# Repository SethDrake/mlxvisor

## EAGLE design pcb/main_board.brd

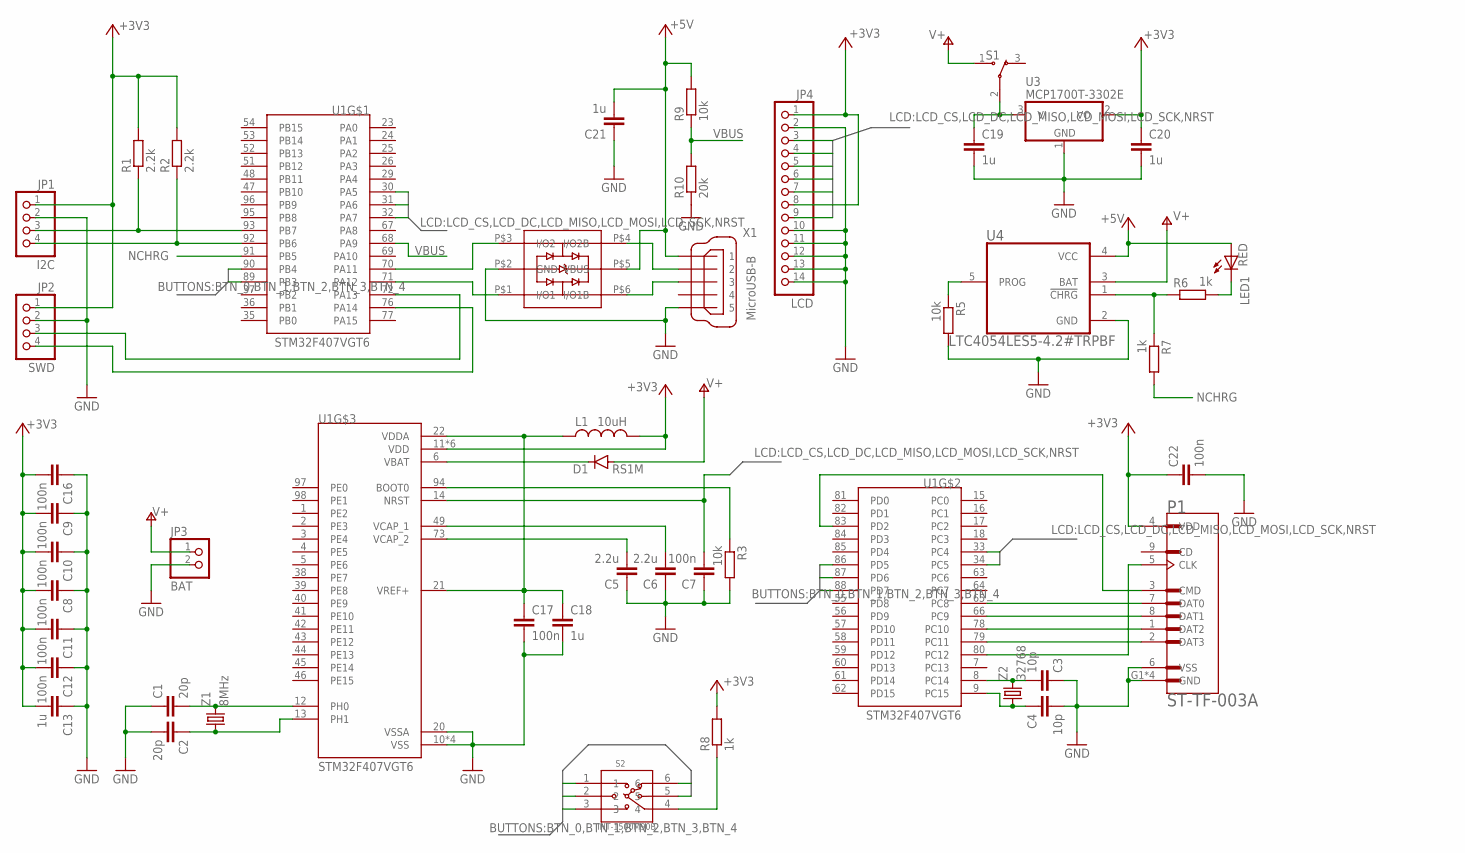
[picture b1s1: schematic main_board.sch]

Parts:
C1, C2: 20p; C0805
C3, C4: 10p; C0805
C5, C6: 2.2u; C0805
C7, C8, C9, C10, C11, C12, C16, C17, C22: 100n; C0805
C13, C18, C19, C20, C21: 1u; C0805
D1: RS1M; DO-214AC
JP1: I2C; 1X04
JP2: SWD; 1X04
JP3: BAT; 1X02
JP4: LCD; 1X14
L1: 10uH; L2012C
LED1: RED; CHIP-LED0805
P1: ST-TF-003A; SUNTECH_ST-TF-003A
R1, R2: 2.2k; R0805
R3, R5, R9: 10k; R0805
R6, R7, R8: 1k; R0805
R10: 20k; R0805
S1: SSA12G; SW_SSA12G
S2: INT-1500M90B; SW6-3.25-10X10X8.6MM
U1: STM32F407VGT6; QFP50P1600X1600X160-100N
U2: USBLC6-2; SOT-23-6L
U3: MCP1700T-3302E; SOT23
U4: LTC4054LES5-4.2#TRPBF; SOT95P280X100-5N
X1: MicroUSB-B; 32005-201
Z1: 8MHz; HC49UP
Z2: 32768; TC38H

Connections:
+5V: C21.2, LED1.A, R9.2, U2.P$5 (VBUS), U4.4 (VCC), X1.1
BOOT0: R3.1, U1.94 (BOOT0)
BTN_0: S2.6, U1.90 (PB4)
BTN_1: S2.1, U1.89 (PB3)
BTN_2: S2.5, U1.88 (PD7)
BTN_3: S2.3, U1.87 (PD6)
BTN_4: S2.2, U1.86 (PD5)
BTN_COM: R8.1, S2.4
D+: U2.P$6 (I/O1B), X1.3
D+_PROT: U1.71 (PA12), U2.P$1 (I/O1)
D-: U2.P$4 (I/O2B), X1.2
D-_INT: U1.70 (PA11), U2.P$3 (I/O2)
GND: C1.1, C2.2, C3.1, C4.2, C5.1, C6.1, C7.1, C8.1, C9.1, C10.1, C11.1, C12.1, C13.1, C16.1, C17.2, C18.2, C19.2, C20.2, C21.1, C22.2, JP1.2, JP2.2, JP3.2, JP4.2, JP4.10, JP4.11, JP4.12, JP4.13, JP4.14, P1.6 (VSS), P1.G1 (GND), P1.G2 (GND), P1.G3 (GND), P1.G4 (GND), R3.2, R5.2, R10.1, U1.10 (VSS), U1.20 (VSSA), U1.27 (VSS), U1.74 (VSS), U1.99 (VSS), U2.P$2 (GND), U3.1 (GND), U4.2 (GND), X1.5
I2C_SCL: JP1.4, R2.1, U1.92 (PB6)
I2C_SDA: JP1.3, R1.1, U1.93 (PB7)
LCD_CS: JP4.3, U1.33 (PC4)
LCD_DC: JP4.5, U1.34 (PC5)
LCD_MISO: JP4.9, U1.31 (PA6)
LCD_MOSI: JP4.6, U1.32 (PA7)
LCD_SCK: JP4.7, U1.30 (PA5)
unnamed: C1.2, U1.12 (PH0), Z1.2
unnamed: C2.1, U1.13 (PH1), Z1.1
unnamed: C4.1, U1.9 (PC15), Z2.1
unnamed: C6.2, U1.49 (VCAP_1)
unnamed: C5.2, U1.73 (VCAP_2)
unnamed: C19.1, S1.2, U3.3 (VI)
unnamed: R6.1, R7.1, U4.1 (!CHRG)
unnamed: LED1.C, R6.2
unnamed: D1.C, U1.6 (VBAT)
unnamed: C3.2, U1.8 (PC14), Z2.2
NCHRG: R7.2, U1.91 (PB5)
NRST: C7.2, JP4.4, U1.14 (NRST)
PROG: R5.1, U4.5 (PROG)
SD_CLK: P1.5 (CLK), U1.80 (PC12)
SD_CMD: P1.3 (CMD), U1.83 (PD2)
SD_DAT0: P1.7 (DAT0), U1.65 (PC8)
SD_DAT1: P1.8 (DAT1), U1.66 (PC9)
SD_DAT2: P1.1 (DAT2), U1.78 (PC10)
SD_DAT3: P1.2 (DAT3), U1.79 (PC11)
SWCLK: JP2.4, U1.76 (PA14)
SWDIO: JP2.3, U1.72 (PA13)
VBAT+: D1.A, JP3.1, S1.1, U4.3 (BAT)
VBUS: R9.1, R10.2, U1.68 (PA9)
VDD: C8.2, C9.2, C10.2, C11.2, C12.2, C13.2, C16.2, C20.1, C22.1, JP1.1, JP2.1, JP4.1, JP4.8, L1.2, P1.4 (VDD), R1.2, R2.2, R8.2, U1.11 (VDD), U1.19 (VDD), U1.28 (VDD), U1.50 (VDD), U1.75 (VDD), U1.100 (VDD), U3.2 (VO)
VDDA: C17.1, C18.1, L1.1, U1.21 (VREF+), U1.22 (VDDA)

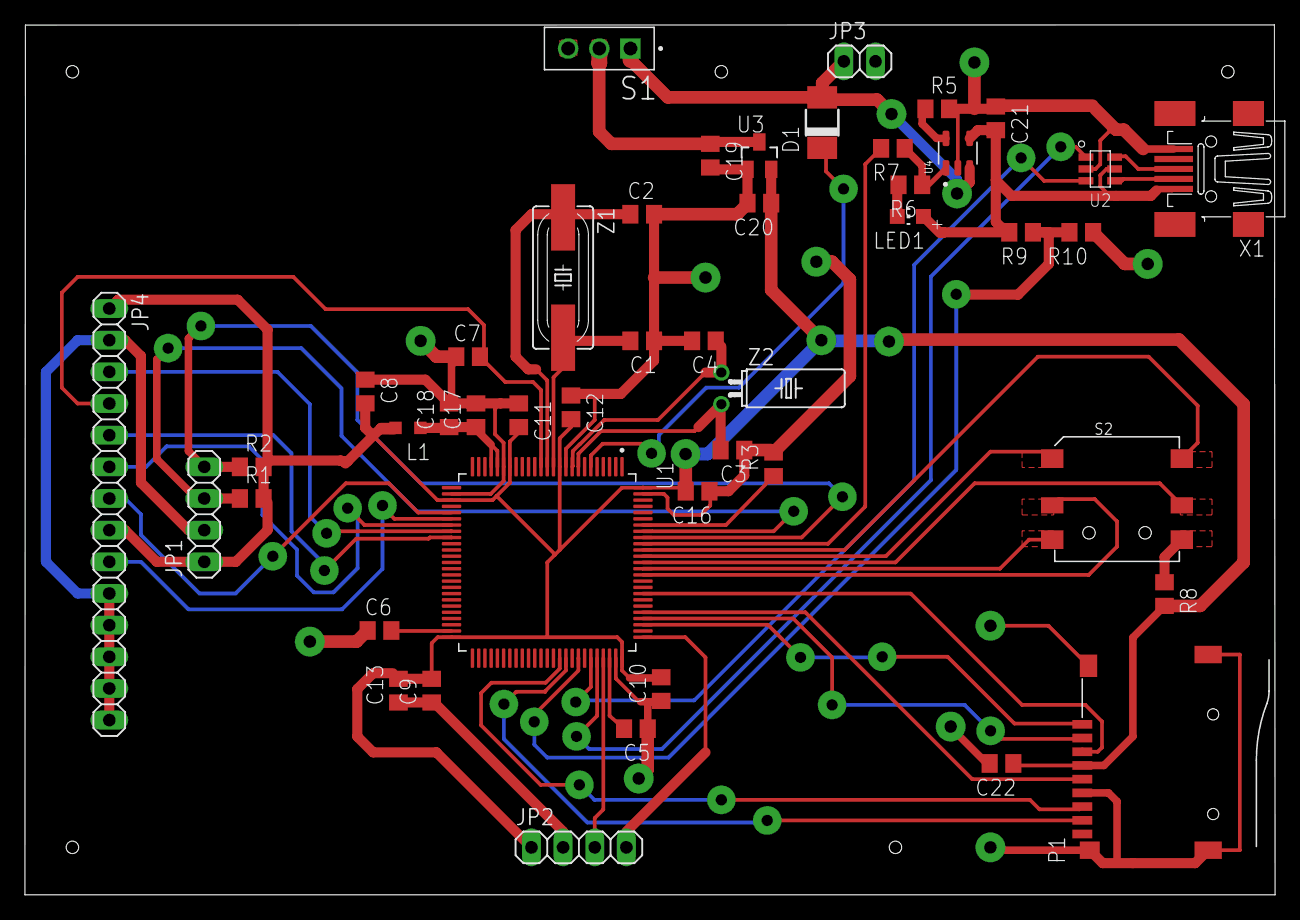
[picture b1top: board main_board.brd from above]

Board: 2 copper layers, 100.3 x 69.8 mm, 46 parts (0 on the bottom side), 45 nets.

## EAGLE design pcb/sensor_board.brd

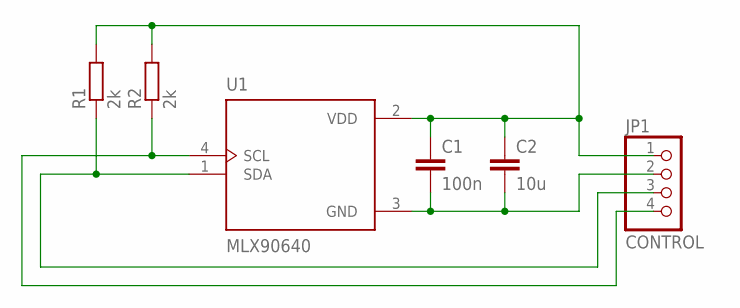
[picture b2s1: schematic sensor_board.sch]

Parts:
C1: 100n; C0805
C2: 10u; C0805
JP1: CONTROL; 1X04
R1, R2: 2k; R0805
U1: MLX90640; TO292P945H1165-4

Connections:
GND: C1.2, C2.2, JP1.2, U1.3 (GND)
SCL: JP1.4, R2.1, U1.4 (SCL)
SDA: JP1.3, R1.1, U1.1 (SDA)
VDD: C1.1, C2.1, JP1.1, R1.2, R2.2, U1.2 (VDD)

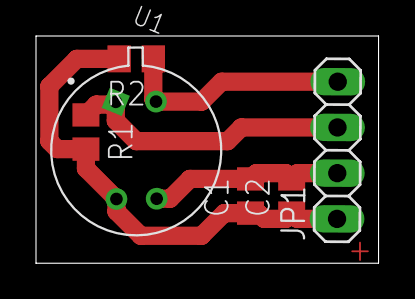
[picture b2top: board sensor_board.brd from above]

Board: 2 copper layers, 19.0 x 12.6 mm, 6 parts (0 on the bottom side), 4 nets.

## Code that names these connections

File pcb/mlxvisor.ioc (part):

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Mcu.Name=STM32F407V(E-G)Tx
Mcu.Package=LQFP100
Mcu.UserName=STM32F407VGTx
PA0-WKUP.Signal=GPIO_Input
PA1.Signal=GPIO_Input
PA11.Mode=Device_Only
PA11.Signal=USB_OTG_FS_DM
PA12.Mode=Device_Only
PA12.Signal=USB_OTG_FS_DP
PA13.Mode=Serial_Wire
PA13.Signal=SYS_JTMS-SWDIO
PA14.Mode=Serial_Wire
PA14.Signal=SYS_JTCK-SWCLK
PA2.Signal=GPIO_Input
PA3.Signal=GPIO_Input
PA4.Signal=GPIO_Input
PA5.Mode=Full_Duplex_Master
PA5.Signal=SPI1_SCK
PA6.Mode=Full_Duplex_Master
PA6.Signal=SPI1_MISO
PA7.Mode=Full_Duplex_Master
PA7.Signal=SPI1_MOSI
PA9.Mode=Activate_VBUS
PA9.Signal=USB_OTG_FS_VBUS
PB3.Signal=GPIO_Input
PB4.Signal=GPIO_Input
PB5.Signal=GPIO_Input
PB6.GPIOParameters=GPIO_Pu
PB6.GPIO_Pu=GPIO_PULLUP
PB6.Mode=I2C
PB6.Signal=I2C1_SCL
PB7.GPIOParameters=GPIO_Pu
PB7.GPIO_Pu=GPIO_PULLUP
PB7.Mode=I2C
PB7.Signal=I2C1_SDA
PC10.Mode=SD_4_bits_Wide_bus
PC10.Signal=SDIO_D2
PC11.Mode=SD_4_bits_Wide_bus
PC11.Signal=SDIO_D3
PC12.Mode=SD_4_bits_Wide_bus
PC12.Signal=SDIO_CK
PC14-OSC32_IN.Mode=LSE-External-Oscillator
PC14-OSC32_IN.Signal=RCC_OSC32_IN
PC15-OSC32_OUT.Mode=LSE-External-Oscillator
PC15-OSC32_OUT.Signal=RCC_OSC32_OUT
PC4.Signal=GPIO_Output
PC5.Signal=GPIO_Output
PC8.Mode=SD_4_bits_Wide_bus
PC8.Signal=SDIO_D0
PC9.Mode=SD_4_bits_Wide_bus
PC9.Signal=SDIO_D1
PD2.Mode=SD_4_bits_Wide_bus
PD2.Signal=SDIO_CMD
PD5.Signal=GPIO_Input
PD6.Signal=GPIO_Input
PD7.Signal=GPIO_Input
PH0-OSC_IN.Mode=HSE-External-Oscillator
PH0-OSC_IN.Signal=RCC_OSC_IN
PH1-OSC_OUT.Mode=HSE-External-Oscillator
PH1-OSC_OUT.Signal=RCC_OSC_OUT
RCC.HSE_VALUE=8000000
RCC.SYSCLKFreq_VALUE=240000000
RCC.SYSCLKSource=RCC_SYSCLKSOURCE_PLLCLK
board=custom

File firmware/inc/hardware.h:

#pragma once 
#ifndef __HARDWARE_H
#define __HARDWARE_H

#include "FreeRTOSConfig.h"
#include "stm32f4xx_hal.h"
#include "usbd_def.h"

#ifdef __cplusplus
 extern "C" {
#endif

#define SRAM2 __attribute__((section(".ram2"))) 
#define CCMRAM __attribute__((section(".ccmram"))) 

#define THERMAL_SCALE 7

#define I2C1_SPEED          1000000
#define SPI1_PRESCALER      SPI_BAUDRATEPRESCALER_2
#define SPI1_PRESCALER_SLOW SPI_BAUDRATEPRESCALER_16

#define I2C1_SCL_PORT		GPIOB
#define I2C1_SCL_PIN		GPIO_PIN_6
#define I2C1_SDA_PORT		GPIOB
#define I2C1_SDA_PIN		GPIO_PIN_7

#define SPI1_MOSI_PORT		GPIOA
#define SPI1_MOSI_PIN		GPIO_PIN_7
#define SPI1_MISO_PORT		GPIOA
#define SPI1_MISO_PIN		GPIO_PIN_6
#define SPI1_SCK_PORT		GPIOA
#define SPI1_SCK_PIN		GPIO_PIN_5

#define SPI1_TX_DMA_CHL     DMA_CHANNEL_3
#define SPI1_TX_DMA_STRM    DMA2_Stream5
#define SPI1_TX_DMA_IRQ     DMA2_Stream5_IRQn

#define ADC1_DMA_CHL        DMA_CHANNEL_2
#define ADC1_DMA_STRM       DMA2_Stream0
#define ADC1_DMA_IRQ        DMA2_Stream0_IRQn

#define SD_TX_RX_DMA_CHL    DMA_CHANNEL_4
#define SD_TX_RX_DMA_STRM   DMA2_Stream6  
#define SD_TX_RX_IRQn       DMA2_Stream6_IRQn

#define LCD_CS_PORT			GPIOC
#define LCD_CS_PIN			GPIO_PIN_4
#define LCD_DC_PORT			GPIOC
#define LCD_DC_PIN			GPIO_PIN_5

#define USR_BTN_OK_PORT		GPIOB
#define USR_BTN_OK_PIN		GPIO_PIN_4
#define USR_BTN_U_PORT		GPIOB
#define USR_BTN_U_PIN		GPIO_PIN_3
#define USR_BTN_R_PORT		GPIOD
#define USR_BTN_R_PIN		GPIO_PIN_7
#define USR_BTN_D_PORT		GPIOD
#define USR_BTN_D_PIN		GPIO_PIN_6
#define USR_BTN_L_PORT		GPIOD
#define USR_BTN_L_PIN		GPIO_PIN_5

#define NCHRG_PORT			GPIOB
#define NCHRG_PIN			GPIO_PIN_5

#define VBUS_PORT			GPIOA
#define VBUS_PIN			GPIO_PIN_9

#define USB_PORT			GPIOA
#define USB_DM_PIN			GPIO_PIN_11
#define USB_DP_PIN			GPIO_PIN_12

#define SD_CLKDIV		    10 

#define SDIO_D0_PORT		GPIOC
#define SDIO_D0_PIN			GPIO_PIN_8
#define SDIO_D1_PORT		GPIOC
#define SDIO_D1_PIN			GPIO_PIN_9
#define SDIO_D2_PORT		GPIOC
#define SDIO_D2_PIN			GPIO_PIN_10
#define SDIO_D3_PORT		GPIOC
#define SDIO_D3_PIN			GPIO_PIN_11
#define SDIO_CK_PORT		GPIOC
#define SDIO_CK_PIN			GPIO_PIN_12
#define SDIO_CMD_PORT		GPIOD
#define SDIO_CMD_PIN		GPIO_PIN_2

#define MSD_OK                        ((uint8_t)0x00)
#define MSD_ERROR                     ((uint8_t)0x01)
#define MSD_ERROR_SD_NOT_PRESENT      ((uint8_t)0x02)

#define RTC_ASYNCH_PREDIV       127
#define RTC_SYNCH_PREDIV        255
  
extern I2C_HandleTypeDef	i2c1;
extern SPI_HandleTypeDef	spi1;
extern RTC_HandleTypeDef	rtc;
extern ADC_HandleTypeDef	adc1;
extern SD_HandleTypeDef     sdio;
extern PCD_HandleTypeDef	hpcd;
extern USBD_HandleTypeDef   hUsbDeviceFS;

void	Clock_Init(void);
void	RTC_Config(void);
void	GPIO_Init(void);
void	I2C_Init(void);
void	SPI_Init(void);
void	ADC_Init(void);
uint8_t SDCard_Init(void);
void	DMA_Init(void);
void	USB_Init(void);

void    GPIO_WritePin(GPIO_TypeDef* port, uint16_t pin, uint8_t state);
void    GPIO_TogglePin(GPIO_TypeDef* port, uint16_t pin);
uint8_t GPIO_ReadPin(GPIO_TypeDef* port, uint16_t pin);

void	GetDateTime(RTC_DateTypeDef* date, RTC_TimeTypeDef* time);
void	SaveDateTime(RTC_DateTypeDef* date, RTC_TimeTypeDef* time);

/* static buffers */
extern uint16_t framebuffer[24 * THERMAL_SCALE * 32 * THERMAL_SCALE];
extern uint16_t gradientFb[10 * 24 * THERMAL_SCALE];
extern uint16_t batteryFb[48 * 14];

extern uint16_t mlxEE[832];
extern uint16_t frameData[834];
extern uint16_t charbuf[128];
extern float dots[24 * 32];

#ifdef __cplusplus
}
#endif

#endif /* __HARDWARE_H */

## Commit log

2022-01-20 in progress
2022-01-21 i2c bus and sensor reading ready
2022-01-21 lcd via spi in progress
2022-01-22 lcd via spi base functionality
2022-01-22 lcd via spi + dma ir sensor based func
2022-01-22 work in progress..
2022-01-23 datasheets
2022-01-24 schematics in progress..
2022-01-26 pcb in progress..
2022-01-27 pcb almost done
2022-01-27 pcb completed
2022-02-19 updated pcb printouts
2022-02-20 mask
2022-02-20 correct board errors
2022-02-21 prototype 1
2022-02-23 sensor board
2022-02-24 rotate sensor image to 180 deg
2022-02-24 ver 0.2 fw ready
2022-02-26 link to fusion 360
2022-02-26 fix scheme error
2022-02-28 enclosure + fw improvements
2022-03-01 updated project structure
2022-03-01 additional features
2022-03-04 last enclosure version ans small fw changes
2022-03-05 settings screen
2022-03-05 small refactoring
2022-03-06 sdcard support in progress..
2022-03-07 rtos heap to ccmram, buffers to sram2
2022-03-07 sdcard basic support
2022-03-07 files list screen
2022-03-07 file view screen
2022-03-07 file save functionality fix
2022-03-07 bugfix
2022-03-09 adc vbat correction
2022-03-11 usb mass storage device
2022-03-11 fixed usb msd and charge indicator
2022-03-11 small fixes
2022-03-14 small optimizations sdio dma disabled
2022-03-20 disable profiling
2022-03-24 fixed LSE configuration error
2022-03-24 moved ffconf.h to inc
